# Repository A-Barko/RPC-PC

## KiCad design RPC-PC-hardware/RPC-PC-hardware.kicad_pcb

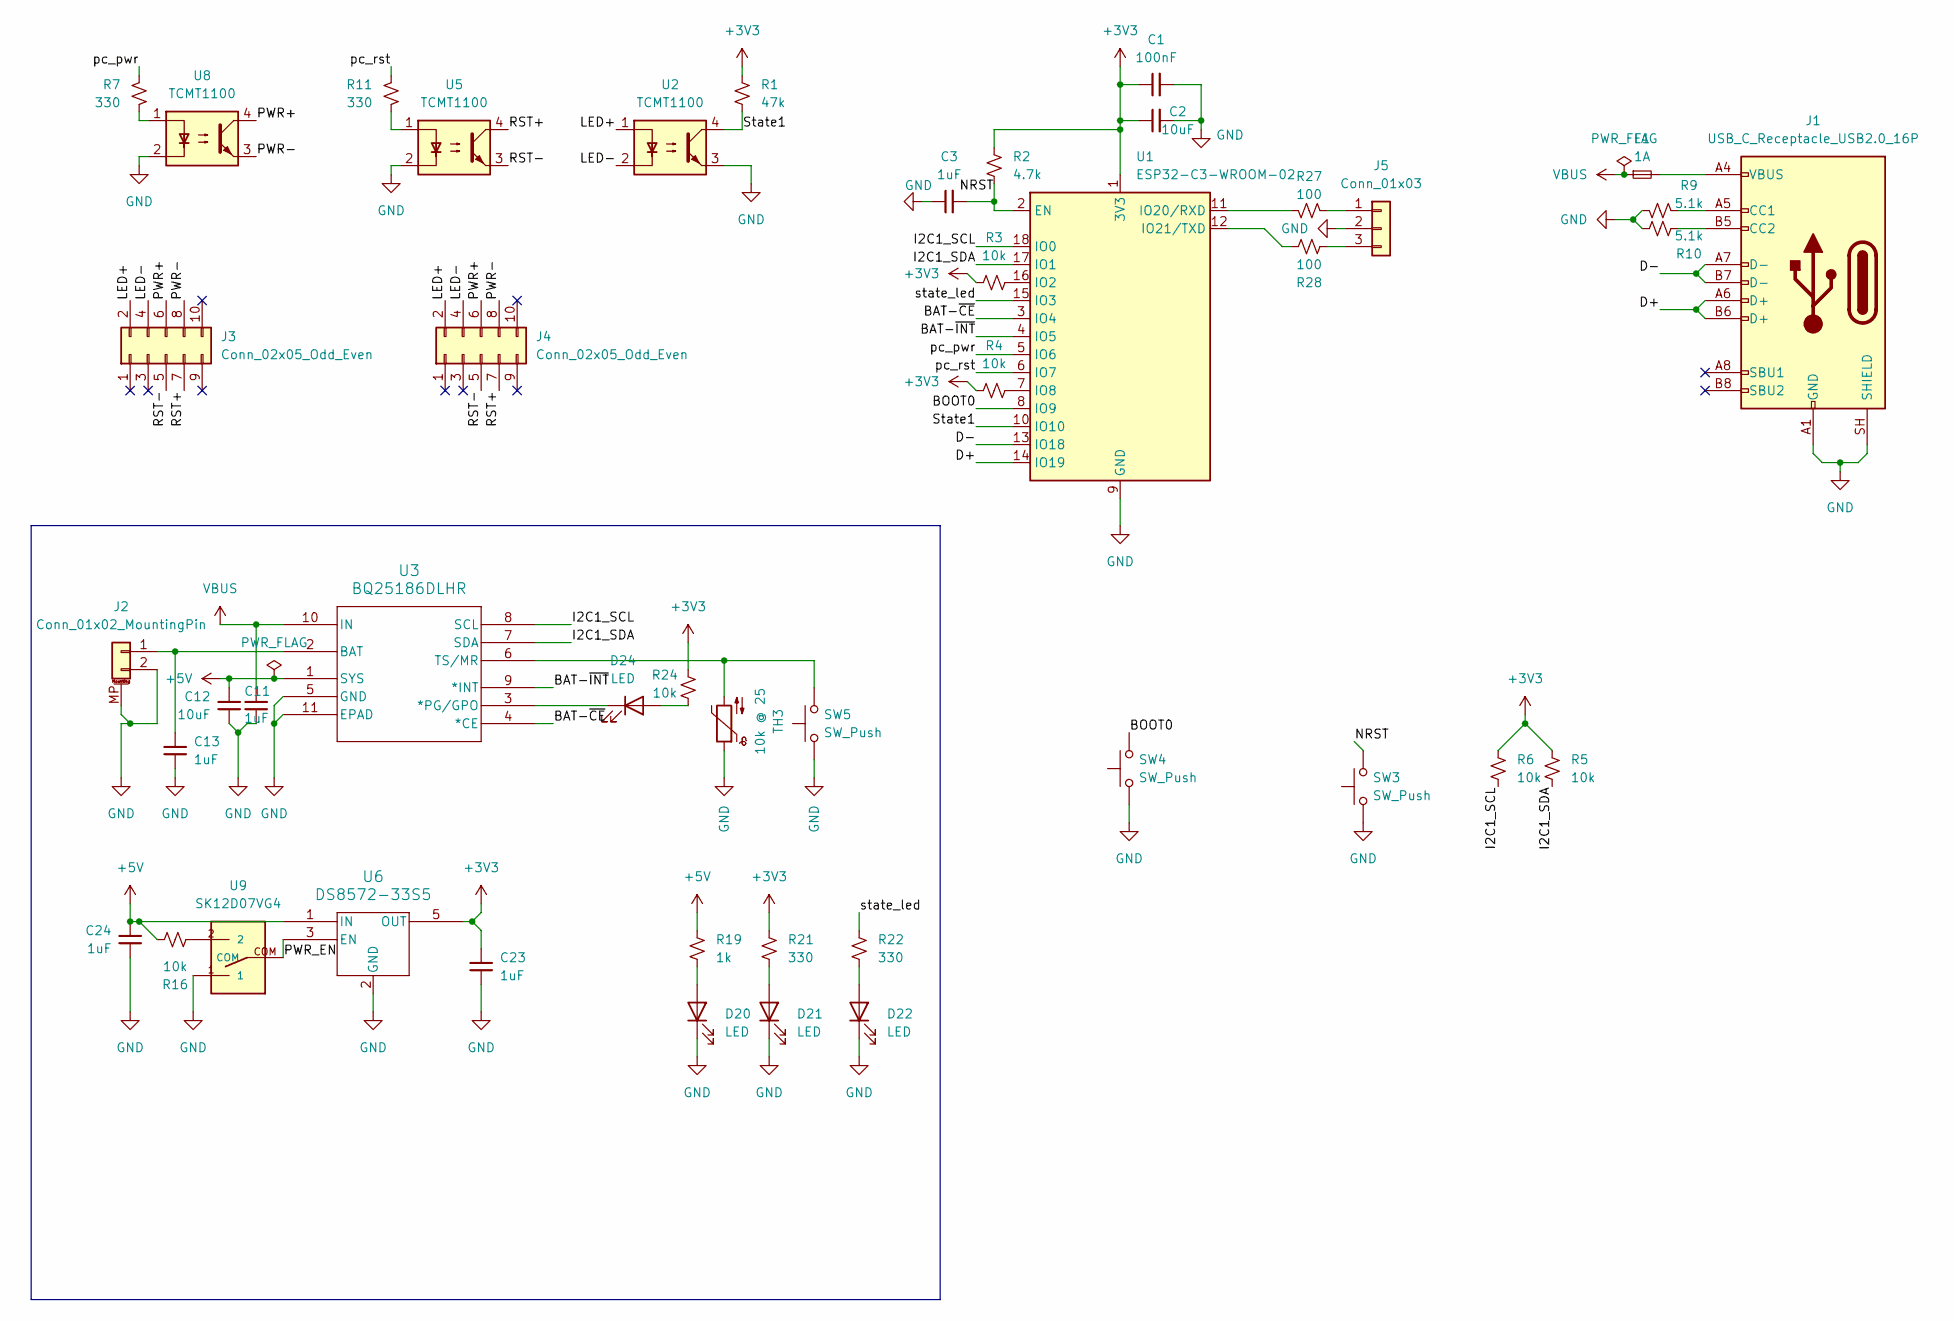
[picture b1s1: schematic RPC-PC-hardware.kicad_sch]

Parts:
C1: 100nF; C_0603_1608Metric
C2, C12: 10uF; C_0603_1608Metric
C3, C11, C13, C23, C24: 1uF; C_0603_1608Metric
D20, D21, D22, D24: LED; LED_0603_1608Metric
F1: 1A; Fuse_0603_1608Metric
J1: USB_C_Receptacle_USB2.0_16P; USB_C_Receptacle_HCTL_HC-TYPE-C-16P-01A
J2: Conn_01x02_MountingPin; JST_PH_S2B-PH-K_1x02_P2.00mm_Horizontal
J3, J4: Conn_02x05_Odd_Even; PinHeader_2x05_P2.54mm_Vertical
J5: Conn_01x03; PinHeader_1x03_P2.54mm_Vertical
R1: 47k; R_0603_1608Metric
R2: 4.7k; R_0603_1608Metric
R3, R4, R5, R6, R16, R24: 10k; R_0603_1608Metric
R7, R11, R21, R22: 330; R_0603_1608Metric
R9, R10: 5.1k; R_0603_1608Metric
R19: 1k; R_0603_1608Metric
R27, R28: 100; R_0603_1608Metric
SW3, SW4, SW5: SW_Push; button_smol
TH3: 10k @ 25; R_0805_2012Metric
U1: ESP32-C3-WROOM-02
U2, U5, U8: TCMT1100; SOP-4_4.4x2.6mm_P1.27mm
U3: BQ25186DLHR; WSON10_2P2X2_TEX
U6: DS8572-33S5; SOT_233DBVR_TEX
U9: SK12D07VG4

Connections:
+3V3: C1.1, C2.1, C23.1, R1.1, R2.1, R3.1, R4.1, R5.2, R6.2, R21.1, R24.2, U1.1 (3V3), U6.5 (OUT)
+5V: C12.1, C24.1, R16.1, R19.1, U3.1 (SYS), U6.1 (IN)
/BAT-~CE: U1.3 (IO4), U3.4 (*CE)
/BAT-~INT: U1.4 (IO5), U3.9 (*INT)
/BOOT0: SW4.2, U1.8 (IO9)
/D+: J1.A6 (D+), J1.B6 (D+), U1.14 (IO19)
/D-: J1.A7 (D-), J1.B7 (D-), U1.13 (IO18)
/I2C1_SCL: R6.1, U1.18 (IO0), U3.8 (SCL)
/I2C1_SDA: R5.1, U1.17 (IO1), U3.7 (SDA)
/LED+: J3.2, J4.2, U2.1
/LED-: J3.4, J4.4, U2.2
/NRST: C3.2, R2.2, SW3.2, U1.2 (EN)
/PWR+: J3.6, J4.6, U8.4
/PWR-: J3.8, J4.8, U8.3
/PWR_EN: U6.3 (EN), U9.COM
/RST+: J3.7, J4.7, U5.4
/RST-: J3.5, J4.5, U5.3
/State1: R1.2, U1.10 (IO10), U2.4
/pc_pwr: R7.1, U1.5 (IO6)
/pc_rst: R11.1, U1.6 (IO7)
/state_led: R22.1, U1.15 (IO3)
GND: C1.2, C2.2, C3.1, C11.2, C12.2, C13.2, C23.2, C24.2, D20.1 (K), D21.1 (K), D22.1 (K), J1.A1 (GND), J1.A12 (GND), J1.B1 (GND), J1.B12 (GND), J1.SH (SHIELD), J2.2, J2.MP (MountPin), J5.2, R9.2, R10.2, SW3.1, SW4.1, SW5.1, TH3.1, U1.9 (GND), U1.19 (GND), U2.3, U3.5 (GND), U3.11 (EPAD), U5.2, U6.2 (GND), U8.2, U9.1; also elsewhere on the board
unnamed: D20.2 (A), R19.2
unnamed: D21.2 (A), R21.2
unnamed: D22.2 (A), R22.2
unnamed: D24.2 (A), R24.1
unnamed: D24.1 (K), U3.3 (*PG/GPO)
unnamed: F1.2, J1.A4 (VBUS), J1.A9 (VBUS), J1.B4 (VBUS), J1.B9 (VBUS)
unnamed: J1.A5 (CC1), R9.1
unnamed: J1.B5 (CC2), R10.1
unnamed 30: C13.1, J2.1, U3.2 (BAT); also elsewhere on the board
unnamed: J5.1, R27.1
unnamed: J5.3, R28.1
unnamed: R7.2, U8.1
unnamed: R11.2, U5.1
unnamed: R16.2, U9.2
unnamed: R3.2, U1.16 (IO2)
unnamed: R4.2, U1.7 (IO8)
unnamed: R27.2, U1.11 (IO20/RXD)
unnamed: R28.2, U1.12 (IO21/TXD)
unnamed: SW5.2, TH3.2, U3.6 (TS/MR)
VBUS: C11.1, F1.1, U3.10 (IN)

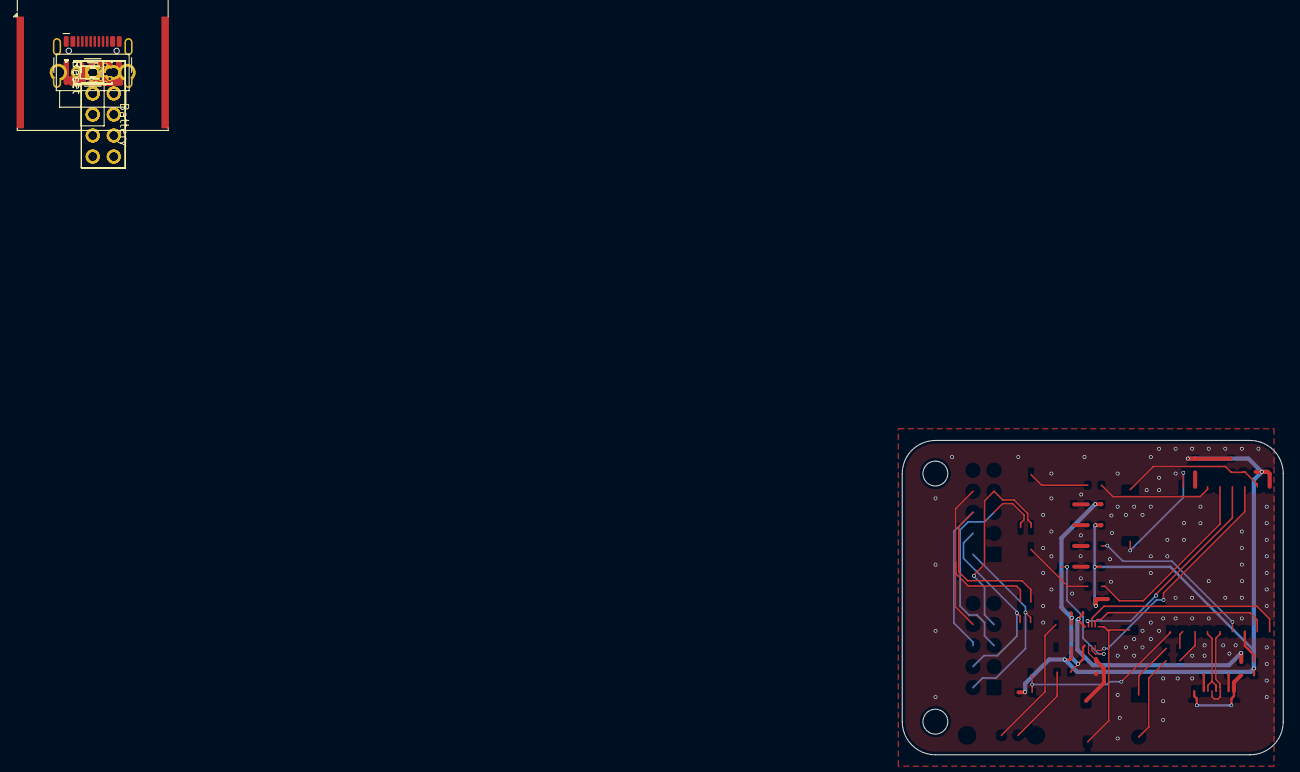
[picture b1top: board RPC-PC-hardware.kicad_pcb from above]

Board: 2 copper layers, 46.0 x 38.0 mm, 46 parts (1 on the bottom side), 42 nets.

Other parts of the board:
+  -: Conn_01x02_MountingPin; JST_PH_S2B-PH-K_1x02_P2.00mm_Horizontal

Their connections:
GND: + -.2; also elsewhere on the board
unnamed 30: + -.1; also elsewhere on the board
